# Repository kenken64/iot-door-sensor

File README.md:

# Door/Window Sensor - Internet of Things

## Tindie Store - Order the device here https://bit.ly/2L2vBSy 

### If you would like to see further enhancement of this whole iot platform kindly donate to my BTC account

Nothing spells security than being notified or alerted if somebody has entered your premises without your permission. It also helps when even before someone can gain entry, you already know who he or she is. The main idea of this door/window sensor is to simply provide you information if someone has gone through any of your property entry points.

## Works with Many Entry Points

The door/window sensor is primarily used to detect people or objects that have passed through the doors, but it’s also compatible to windows and any enclosures that could be opened.

## Small to Notice

The door/window sensor is a very unassuming device so it blends well with the rest of the commonly found items or appliances in your home. It is also quite small you can easily hide it well, away from the prying eyes of potential intruders, and it doesn’t get in the way with the actual functions of the entry points.

The device is a magnetic switch that allows it to accurately determine location and direction. In other words, there are no false alarms and leads.

## Very Easy and Fast Installation

As a magnetic device, it doesn’t require any intricate tools to install. In fact, you simply need to snap it into any metal part of your entryway, and you can already properly and quickly configure the door sensor. If not, you can conveniently attached even a small piece of metal at any part of the door and window.

## Works on the cloud

A connected home brings devices and services together for an integrated, autonomous experience that improves a consumer’s life. Connected home experiences include everything from window/door sensor , voice-controlled lights, house-cleaning robots, machine learning-enabled security cameras, and WiFi routers that troubleshoot for you. Thanks to decreasing costs and increasing options for connectivity, these smart home devices, sensors, and tools can be interlinked to create real-time, contextual, and smart experiences for consumers.

IoT powers the connected home by bringing new features and capabilities to smart devices, like interconnectivity, security, offline communication, predictive maintenance, analytics for consumer insights, and machine learning. Each of these capabilities play a different role in key connected home use cases such as home automation, home security and monitoring, and home networking.

# Multiple version
- Wifi version
- Sigfox version
- Lorawan version require an existing lorawan gateway (Prototype, too expensive)

# Pre-requisite Lora Gateway
- Use the raspi-config tool (with sudo raspi-config) to enable SPI on the Raspberry Pi
- Install wiringpi (sudo apt-get install wiringpi)

# Pre-requisite microcontroller and parts
- Adafruit Huzzah ESP8266/TTGO ESP32 Wifi/Arduino UNO
- 2-way connector
- LED
- 47k Ohm Resistor
- 10k Ohm Resistor
- 220 Ohm Resistor
- Magnetic Door Sensor
- Jumper
- Custom made PCB by kenken64
- Lipo Battery/ 18650 battery
- Headers 
- UnaShield Sigfox for Arduino UNO

## 3D printed Casing/Housing
- ESP8266/ESP32 STL 3d Design
- Sigfox STL 3d Design

# PCB Design (Eagle and Fritzing)
- WIFI Version 1 (Custom made PCB)
<br>

- WIFI Version 2 (Custom made PCB)
<br>

- Sigfox version (Shield from UnaBiz)

# Pre-requisite software & library

- Microsoft Visual Studio Code
- Node JS
- Ubuntu/Windows 10 ( 2 CPU and 2GB ram )
- Angular 7 Cli
- Arduino IDE
- ESPBattery
- ESP 8266/32 Arduino library
- Unashield Sigfox library

# Pre-requisite Cloud account

- Twilio (require your own credit to send out SMS/WhatsApp)
- Gmail https://mail.google.com/mail/u/0/
- Google Firebase Realtime Database https://console.firebase.google.com/u/0/?pli=1
- Blynk Cloud Service ( Mobile App) 

# Twilio - SMS and WhatsApp Notification

- Create a twilio account and top up with the credits.
- Note down the twilio SSID and AUTH TOKEN.
- Purchase a number from Twilio
- Also note down the WhatsApp from number

# SMTP or Gmail account Email notification

- Create gmail account. Please do not use personal gmail account for this.
- Enable unsecure access to this account [Gmail API setting](https://support.google.com/accounts/answer/6010255?hl=en)

# Backend Server Side (AWS Lightsail/ DO / Azure / Google Cloud)
- Detect door is open and closed.
- Send SMS using twilio to the configure recipient mobile number
- Send notification email to the configure recipient email address
- Detect battery is low send notification via SMS and email
- Log all events to the door's device
- Provide exportable reporting of all doors 

# Environment variable

| Env variables        | Description           | 
| ------------- |:-------------:| 
| SMTP_GMAIL_ACC      | Gmail SMTP account that use to send email to security guard  | 
| SMTP_GMAIL_PASSWORD     | Password for the above email account      |  
| TWILIO_SSID | SSID for the twilio sms APIs      |   
| TWILIO_AUTH_TOKEN | Security token for the twilio sms APIs      | 
| TWILIO_NUMBER | You need a twilio phone number in order to send SMS to the receipient      | 
| FIREBASE_DB_URL | NoSQL Database url     | 
| JOB_INTERVAL | Interval period where the job poll for the changes from firebase and the blynk APIs      | 
| JOB_TIMEOUT | Tiemout period where the job poll for the changes from firebase and the blynk APIs      | 
| NOTIFICATION_ENABLE | Disable and enable notification when door is open and closed      | 
| FIREBASE_SVC_ACC_FILE | Firebase credential file to perform admin operations e.g.  https://door-sensor-proj.firebaseio.com  | 
| CLEAN_UP_SCHEDULE | Schedule timing to cleanup events logs     | 
| BLYNK_API_URL | Blynk IOT API URL  e.g. http://blynk-cloud.com/   | 
| SIGFOX_SERVER_PORT | Sigfox callback backend server port number     |
| TWILIO_WHATSAPP_NO | Twilio WhatsApp from number     |

# Door/Window sensor Web App

## List of door/window installed with sensor

## Add new door/window sensor

## Add new security personel to the system

## Associate multiple security guard to the sensors

## Provide feedback on door/window events

## SMS Notification

## Email Notification

## WhatsApp Notification

## Export as Excel Spreadsheet

# Setup Instructions for the PWA Web App and Backend

Kindly create a Azure/AWS/Google Cloud account to deploy all this component on a Ubuntu 18.04 distribution

After creating a cloud instance, ssh/login into the instance install git software and node js. Please follow the links below with all the installation steps 

https://www.digitalocean.com/community/tutorials/how-to-install-git-on-ubuntu-18-04-quickstart

https://www.digitalocean.com/community/tutorials/how-to-install-node-js-on-ubuntu-18-04

This project was generated with [Angular CLI](https://github.com/angular/angular-cli) version 7.1.4.

## Logon to the newly created cloud server and pull down the github source codes using the below linux command

```
cd ~
git clone https://github.com/kenken64/iot-door-sensor.git
```
## Development server

Run `ng serve` for a dev server. Navigate to `http://localhost:4200/`. The app will automatically reload if you change any of the source files.

## Code scaffolding

Run `ng generate component component-name` to generate a new component. You can also use `ng generate directive|pipe|service|class|guard|interface|enum|module`.

## Build

Run `ng build` to build the project. The build artifacts will be stored in the `dist/` directory. Use the `--prod` flag for a production build.

## Running unit tests

Run `ng test` to execute the unit tests via [Karma](https://karma-runner.github.io).

## Running end-to-end tests

Run `ng e2e` to execute the end-to-end tests via [Protractor](http://www.protractortest.org/).

## Further help

To get more help on the Angular CLI use `ng help` or go check out the [Angular CLI README](https://github.com/angular/angular-cli/blob/master/README.md).

## Install PWA from dist directory to Nginx 

Use the link below for the nginx installation

https://www.digitalocean.com/community/tutorials/how-to-install-nginx-on-ubuntu-18-04

Right after the web server is installed, install free SSL certificate using Let's Encrypt 

https://www.digitalocean.com/community/tutorials/how-to-secure-nginx-with-let-s-encrypt-on-ubuntu-18-04

Lastly, copy all the files from the angular app /dist directory to the nginx web server root directory e.g. /var/www/html

## Google Firebase

It is must to have Google account in order to create a firebase account for this project

1. Create a firebase real time database project following this link https://firebase.google.com/

## Install and start redis server

1. Install redis server

```
sudo apt-get update
sudo apt-get install redis
```

2. Start Redis server

```
sudo service redis-server start
```
3. Check redis server status
```
sudo service redis-server status
```

4. if only there is a crash on the worker process then run flush

```
redis-cli FLUSHALL
```

## Start Backend server
How to start the sms and email backend server that poll the devices.

```
$ cd server/
$ npm i 
$ pm2 start server.js --name server --max-memory-restart 1G --restart-delay 10000 --node-args="--expose-gc --max-old-space-size=4096"
```

## Start Door Sensor Worker Engine to poll door's state
Worker consumes the job from the delegator to check the door sensors and send out notification via SMS/WhatsApp/Email.

Each worker is configured with its own designated door sensor's blynk auth key. Refer to the server/worker-config.json

```
[
    {
        "workerName": "worker1",
        "doors": ["b40605f4f5d5484bbe7b9a3cb78f1376",
                "962d1f57311e47c7bb71697b8051de30",
                "980f92ef13db430594a89315d86dd37b"

        ]
    },
    {
        "workerName": "worker2",
        "doors": [ "185333bfb0d14a2a9365fdc3bd37966a",
                "953b351b1ba4428bb781c40bec29a300",
                "194eab22d2bd49c0a580c01d7d19ce34"
        ]
    },
    {
        "workerName": "worker3",
        "doors": [ "166fff24ab4f4a52a31a936369d3a1cc",
                "2dde80b00cf342c1b6977e91dd9b6039"
        ]
    },
    {
        "workerName": "worker4",
        "doors": [ "c56c9a1ab4b1415998c06173786354f2",
                "2f0b7bd399a54a839e976a09bee2463a"
        ]
    }
]
```

```
$ cd server/
$ pm2 start worker.js --name worker --max-memory-restart 500M -- --workername=worker1 --node-args="--expose-gc
$ pm2 start worker.js --name worker2 --max-memory-restart 500M -- --workername=worker2 --node-args="--expose-gc
$ pm2 start worker.js --name worker3 --max-memory-restart 500M -- --workername=worker3 --node-args="--expose-gc
$ pm2 start worker.js --name worker4 --max-memory-restart 500M -- --workername=worker4 --node-args="--expose-gc
```

## Blynk Configuration

Go to your Google App Store/Apple store search for Blynk, install it

Register an account with Blynk

Create a new project, choose device as ESP8266 WIFI send the auth key to your email address

## Restful API for Blynk

Below is the link to test out the API using your REST client
https://blynkapi.docs.apiary.io/#

## Install firmware to the ESP8266/ESP32

1. Plug the ESP8266 to your computer
2. Launch Arduino IDE , open up the Arduino sketch from the directory /firmware/door_sensor/door_sensor.ino
3. Search for the codes, replace the double quote values according to the auth code from the blynk email from your mailbox
```
char blynk_token[33] = "166fff24ab4f4a52a31a936369d0a1cc";
```
4. Make sure ESP8266 board are installed using the board manager.

5. Select the configuration properly before compiling and flashing the ESP8266. Take note the flash size and port.

5. The following libraries is amust to be installed before sync the firmware to the ESP8266 board
  - ArduinoJson (Take note do not use the latest version)

  - FS

  - ESPBattery (https://github.com/LennartHennigs/ESPBattery)
  - Blynk

  - WifiManager

6. Compile and sync the firmware to the microcontroller board

## Once everything is setup and up running on the cloud

Last thing to do is to power up the door sensor using a micro usb cable, at first if there isn't any wifi setting being configure. the device  will act as an wireless access point with the SSID stated as "AutoAPDoorSensor" Access the portal via the following web address htttp://192.168.244.1

Configure the door sensor device to connect to your own wifi router with credential. Do not change the blynk auth key.

## Check the health of all processes
```
pm2 list
```

## Debug memory leakage
- Use ChromeDev Tools
- Dynatrace (https://www.dynatrace.com/)
- Sentry io (https://sentry.io/welcome/)

## Future work - Integrate with ElectricMagnetic lock 

Most of the EM lock in the market uses 12v AC likely need to enhance the PCB board

https://shopee.sg/Hot-DC-DC-Converter-Output-Power-Adapter-24V-12V-To-5V-USB-Step-Down-Module-i.10885840.691201434?gclid=Cj0KCQjwnKHlBRDLARIsAMtMHDFC6E65QBD9bycE3Slw0D0tBNxFKR-Vn5mH1KITMRHCil_hmbI2bzYaAmgOEALw_wcB

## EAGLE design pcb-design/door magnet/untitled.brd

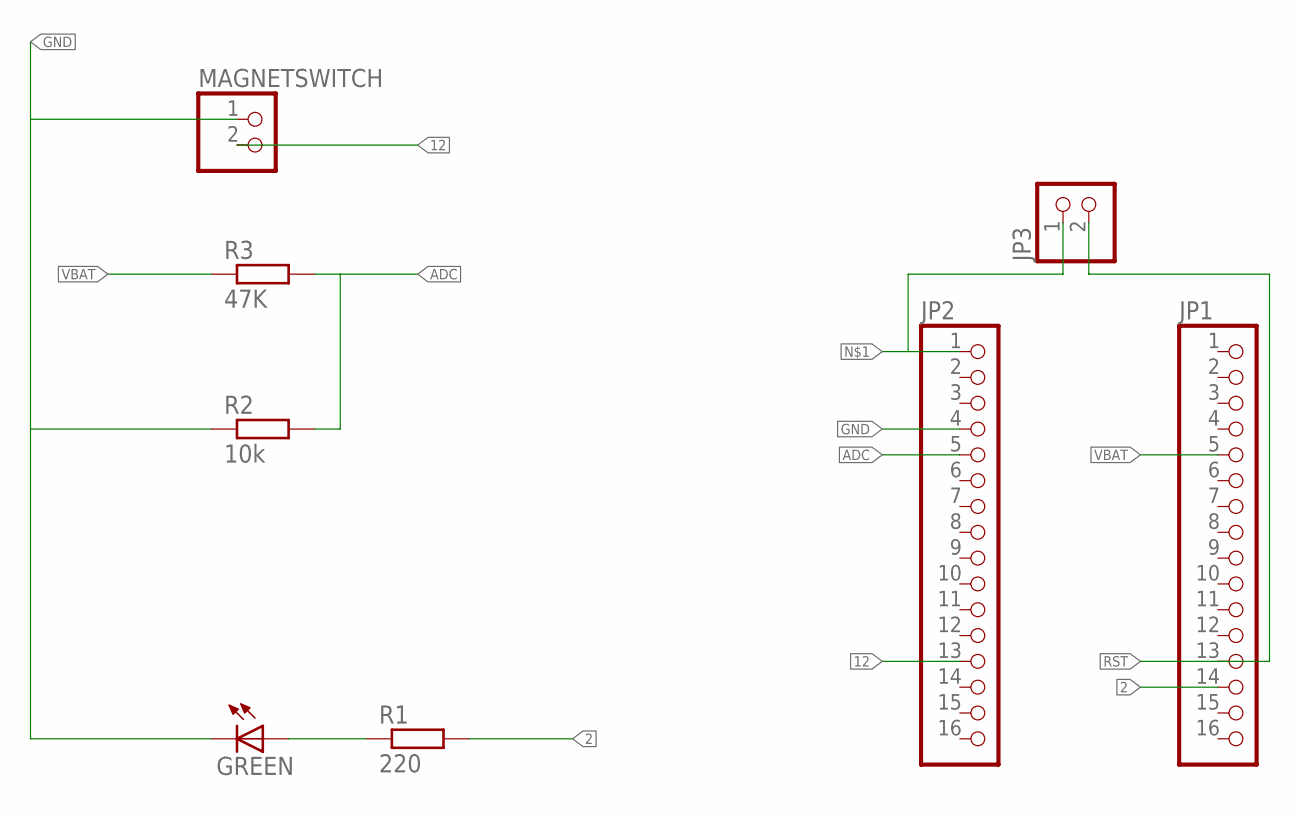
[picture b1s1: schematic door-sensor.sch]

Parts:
GREEN: LED_ELD260; LED_LD260
JP1, JP2: PINHD-1X16; 1X16
JP3: PINHD-1X2; 1X02
MAGNETSWITCH: PINHD-1X2; 1X02
R1: 220; 0204/7
R2: 10k; 0204/7
R3: 47K; 0204/7

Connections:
2: JP1.14, R1.2
12: JP2.13, MAGNETSWITCH.2
ADC: JP2.5, R2.2, R3.2
GND: GREEN.K (C), JP2.4, MAGNETSWITCH.1, R2.1
unnamed: JP2.1, JP3.1
unnamed: GREEN.A, R1.1
RST: JP1.13, JP3.2
VBAT: JP1.5, R3.1

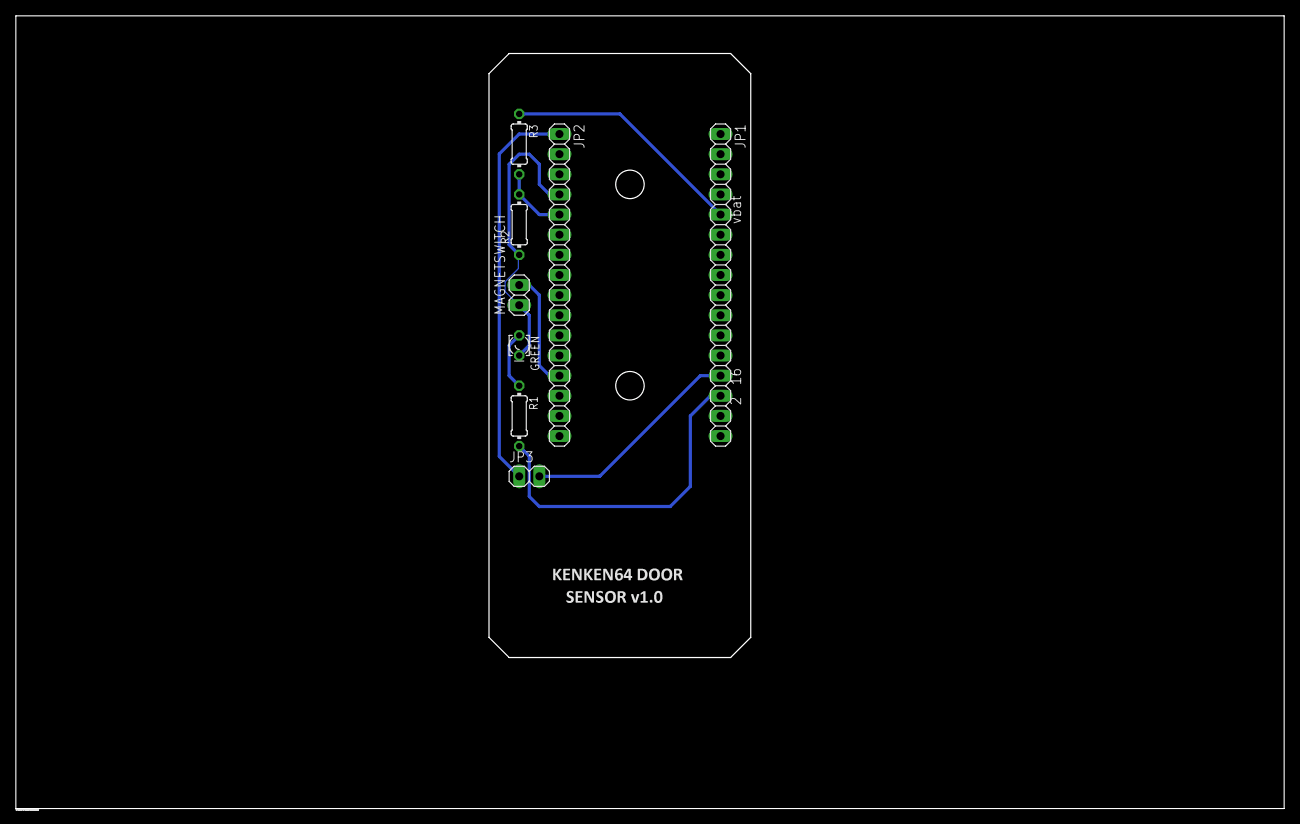
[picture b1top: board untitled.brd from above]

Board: 2 copper layers, 160.0 x 100.0 mm, 8 parts (0 on the bottom side), 8 nets.

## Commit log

2019-01-05 add firmware
2019-01-06 fix the pin
2019-01-07 remove and fixes
2019-01-08 fix security issue
2019-01-09 fixes
2019-01-10 release
2019-01-11 added export excel
2019-01-12 add sound
2019-01-13 fix the battery issue
2019-01-15 fix firmware
2019-01-16 added events
2019-01-17 new fixes
2019-01-22 send pcb to manufacturing
2019-01-23 release v4
2019-01-24 added auth
2019-01-25 release 4
2019-01-29 added battery indicator
2019-01-29 release v6
2019-01-29 release v7
2019-01-29 fix battery bugs
2019-02-04 fix infinite scroll
2019-02-08 fix events
2019-02-11 added feedback
2019-02-11 add feedback on events
2019-02-12 done with feedback
2019-02-12 added filter bottom sheet
2019-02-12 fix undefined on doorRef
2019-02-12 major bugs fixes
2019-02-12 fix the bubble cnt
2019-02-13 completed the badges on the button
2019-02-13 added release9.1
2019-02-13 added filter
2019-02-13 release candidate
2019-02-17 clean up evt
2019-02-17 fix duplicate events
2019-02-17 get guard email at resolver
2019-02-18 fix export excel when snapshot is triggered
2019-02-18 new release
2019-02-21 fix the current time on add feedback
2019-02-22 update release
2019-02-22 fix email timezone issue
2019-03-03 working new protocol
2019-03-04 fix sigfox firmware
2019-03-05 add sigfox server
2019-03-06 fix lorawan
2019-03-07 lora
2019-03-09 fix when rechargeable not available
2019-03-09 fix battery issues with some devices
2019-03-09 added edit door
2019-03-10 release to production
2019-03-13 update icons
2019-03-13 release v1.3
2019-03-14 clean up
2019-03-14 urgent fix
2019-03-14 added sigfox backend server
2019-03-15 added notificatino for sigfox server
2019-03-17 fix a bug
2019-03-17 fix memory leak
2019-03-17 terrible memory leak
2019-03-17 fix connection timeout
2019-03-17 severe memory leak
2019-03-17 still memory leak
2019-03-17 still fixing the leakage
2019-03-18 fix leaks
2019-03-18 queue broker implemented
2019-03-19 added balancing
2019-03-20 fix when timeout return
2019-03-20 fix performance issues
2019-03-21 fix duplicate notification
2019-03-23 partial fix performance issue
2019-03-23 fix perf issues
2019-03-24 never !
2019-03-24 remove gc
2019-03-25 fix send sms and email bugs
2019-03-25 fix destroy subscriber
2019-03-25 release v.1.5.1
2019-03-25 release minor fixes
2019-03-25 fix click on mat item
2019-03-25 bugs bugs
2019-03-29 fix still got one bug
2019-03-30 hope
2019-03-31 stablize fixes
2019-04-08 new stuff
2019-04-08 added eagle schematic
2019-04-08 fix worker
2019-04-09 fix battery check
2019-04-12 ota release
2019-04-12 url https
2019-04-16 fix ota
2019-04-22 brave
2019-04-25 added photo
2019-04-25 final
2019-04-25 added blynk
2019-08-21 uprade to angular 8
